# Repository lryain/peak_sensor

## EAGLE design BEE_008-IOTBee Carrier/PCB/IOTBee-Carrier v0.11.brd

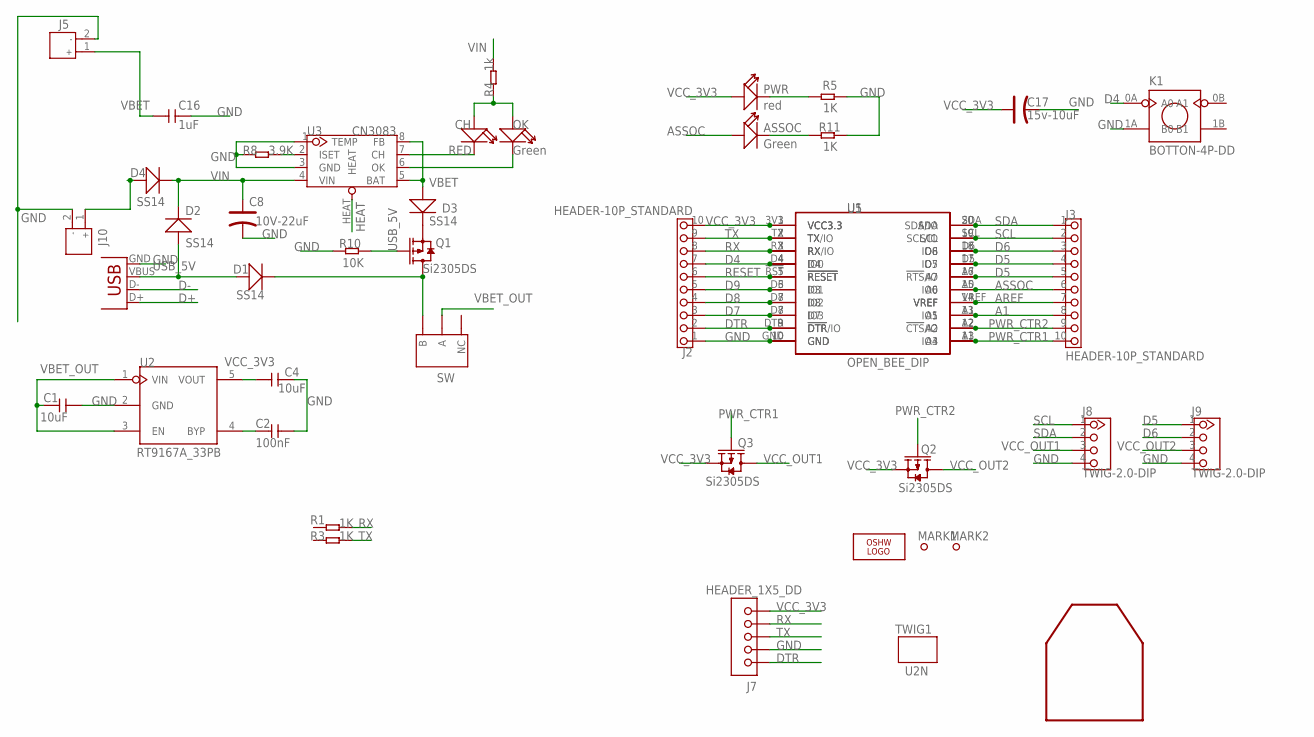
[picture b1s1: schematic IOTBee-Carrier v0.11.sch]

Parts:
ASSOC: Green; D0603
C1, C4: 10uF; 0805
C2: 100nF; 0603
C8: 10V-22uF; AVX-B
C16: 1uF; 0805
C17: 15v-10uF; AVX-A
CH: RED; D0603
D1, D2, D3, D4: SS14; D2010
J2, J3: HEADER-10P_STANDARD; 2.54_10P
J5, J10: JST-2P-POWER-LEADED; 2P-2.0-LEADED-4.7X6.0
J7: HEADER_1X5_DD; CK_1X5
J8, J9: TWIG-2.0-DIP; 2.0_1X4
K1: BOTTON-4P-DD; BTN-S
LOGO2: OSHW_LOGO_FILLX0200-NT; OSHW_FILLX200_NOTEXT
MARK1, MARK2: PAD-MARK; MARK
OK: Green; D0603
PWR: red; D0805
Q1, Q2, Q3: Si2305DS; SOT23
R1, R3, R5, R11: 1K; 0603
R4: 1k; 0603
R8: 3.9K; 0603
R10: 10K; 0603
SW: SWITCH-3P; 008-SW-3P-DIP
TWIG1: U2N; U2N_SILK
U1: OPEN_BEE_DIP; CCBEE-PRO
U2: RT9167A_33PB; SOT23-5
U3: CN3083; SOP8
U5: BEE-IOTBEE-IOTBEE-SOCKET; IOT_BEE_SMD
U$1: WIFI_SILK
X1: USB-SMD-NS; USB-MINIB-NOSTOP

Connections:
A1: J3.8, U1.13 (IO5), U5.A1
AREF: J3.7, U1.14 (VREF), U5.VREF
ASSOC: ASSOC.+, J3.6, U1.15 (IO6), U5.A0
D4: J2.7, K1.0A (A0), U1.4 (IO0), U5.D4
D5: J3.4, J3.5, J9.1, U1.16 (!RTS!/IO), U1.17 (IO7), U5.A7, U5.D5
D6: J3.3, J9.2, U1.18 (IO8), U5.D6
D7: J2.3, U1.8 (IO3), U5.D7
D8: J2.4, U1.7 (IO2), U5.D8
D9: J2.5, U1.6 (IO1), U5.D3
D+: X1.D+
D-: X1.D-
DTR: J2.2, J7.1, U1.9 (!DTR!/IO), U5.DTR (!DTR)
GND: C1.2, C2.2, C4.2, C8.-, C16.2, C17.-, J2.1, J5.2, J7.2, J8.4, J9.4, J10.2, K1.1A (B0), R5.1, R8.1, R10.1, R11.1, U1.10 (GND), U2.2 (GND), U3.1 (TEMP), U3.3 (GND), U5.GND, X1.GND
HEAT: U3.HEAT
unnamed: PWR.-, R5.2
unnamed: R8.2, U3.2 (ISET)
unnamed: D4.+, J10.1
unnamed: C2.1, U2.4 (BYP)
unnamed: CH.-, U3.7 (CH)
unnamed: OK.-, U3.6 (OK)
unnamed: CH.+, OK.+, R4.1
unnamed: D3.-, Q1.2 (S)
unnamed: ASSOC.-, R11.2
unnamed: D1.-, Q1.3 (D), SW.P$3 (B)
PWR_CTR1: J3.10, Q3.1 (G), U1.11 (IO4), U5.A3
PWR_CTR2: J3.9, Q2.1 (G), U1.12 (!CTS!/IO), U5.A2
RESET: J2.6, U1.5 (!RESET), U5.!RST (!RESET)
RX: J2.8, J7.4, R1.2, U1.3 (RX/IO), U5.RX
SCL: J3.2, J8.1, U1.19 (SCL/IO), U5.SCL
SDA: J3.1, J8.2, U1.20 (SDA/IO), U5.SDA
TX: J2.9, J7.3, R3.2, U1.2 (TX/IO), U5.TX
USB_5V: D1.+, D2.+, Q1.1 (G), R10.2, X1.VBUS
VBET: C16.1, D3.+, J5.1, U3.5 (BAT), U3.8 (FB)
VBET_OUT: C1.1, SW.P$2 (A), U2.1 (VIN), U2.3 (EN)
VCC_3V3: C4.1, C17.+, J2.10, J7.5, PWR.+, Q2.2 (S), Q3.2 (S), U1.1 (VCC3.3), U2.5 (VOUT), U5.3V3 (VCC3.3)
VCC_OUT1: J8.3, Q3.3 (D)
VCC_OUT2: J9.3, Q2.3 (D)
VIN: C8.+, D2.-, D4.-, R4.2, U3.4 (VIN)

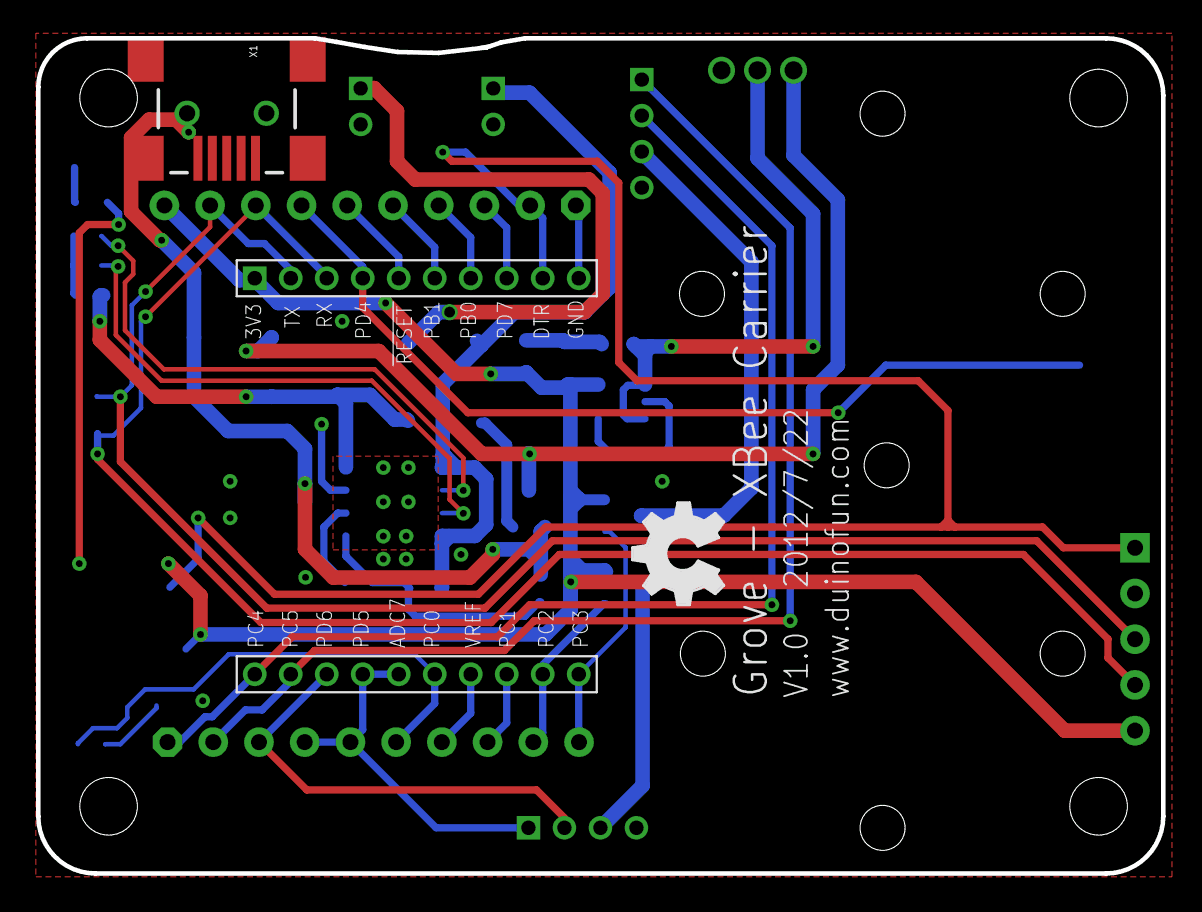
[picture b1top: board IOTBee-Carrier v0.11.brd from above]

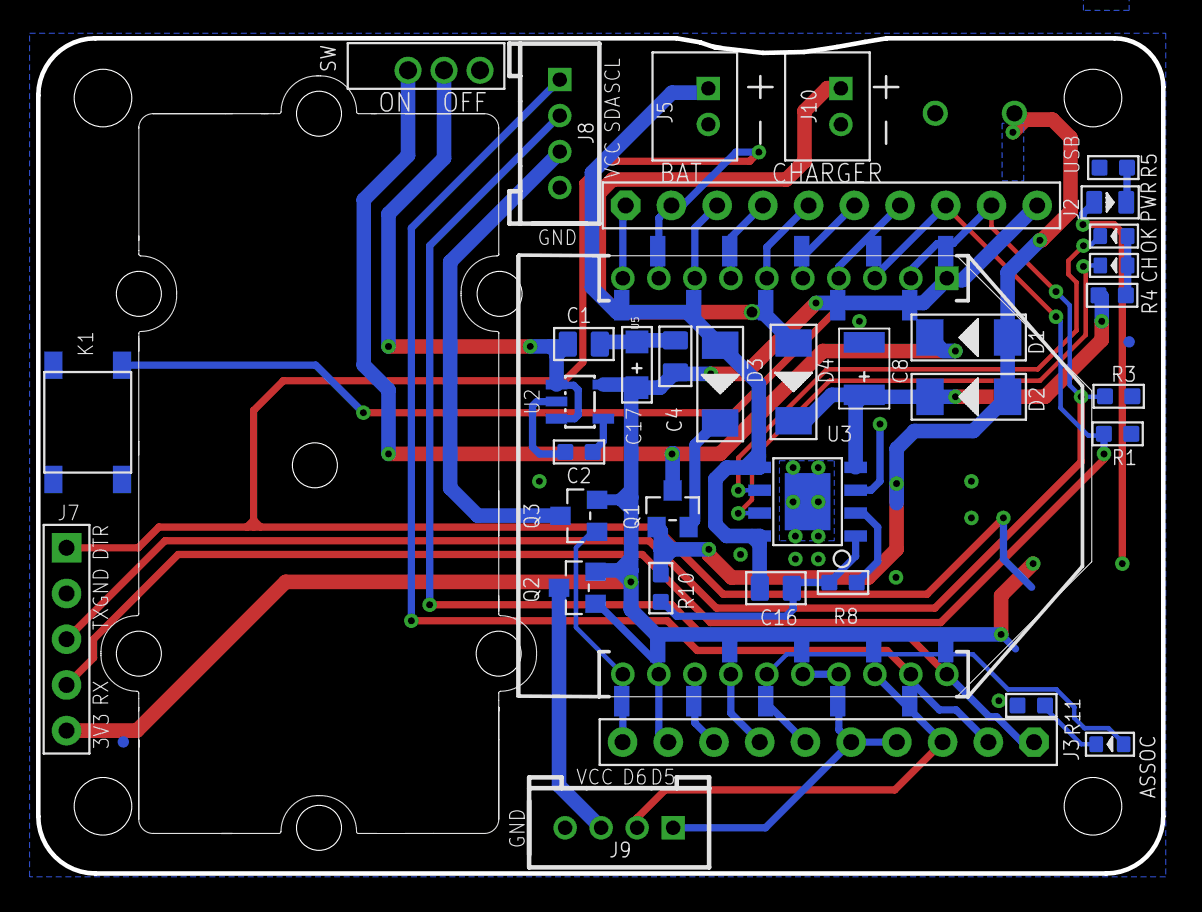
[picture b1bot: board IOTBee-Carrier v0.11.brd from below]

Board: 2 copper layers, 62.5 x 46.5 mm, 43 parts (41 on the bottom side), 35 nets.

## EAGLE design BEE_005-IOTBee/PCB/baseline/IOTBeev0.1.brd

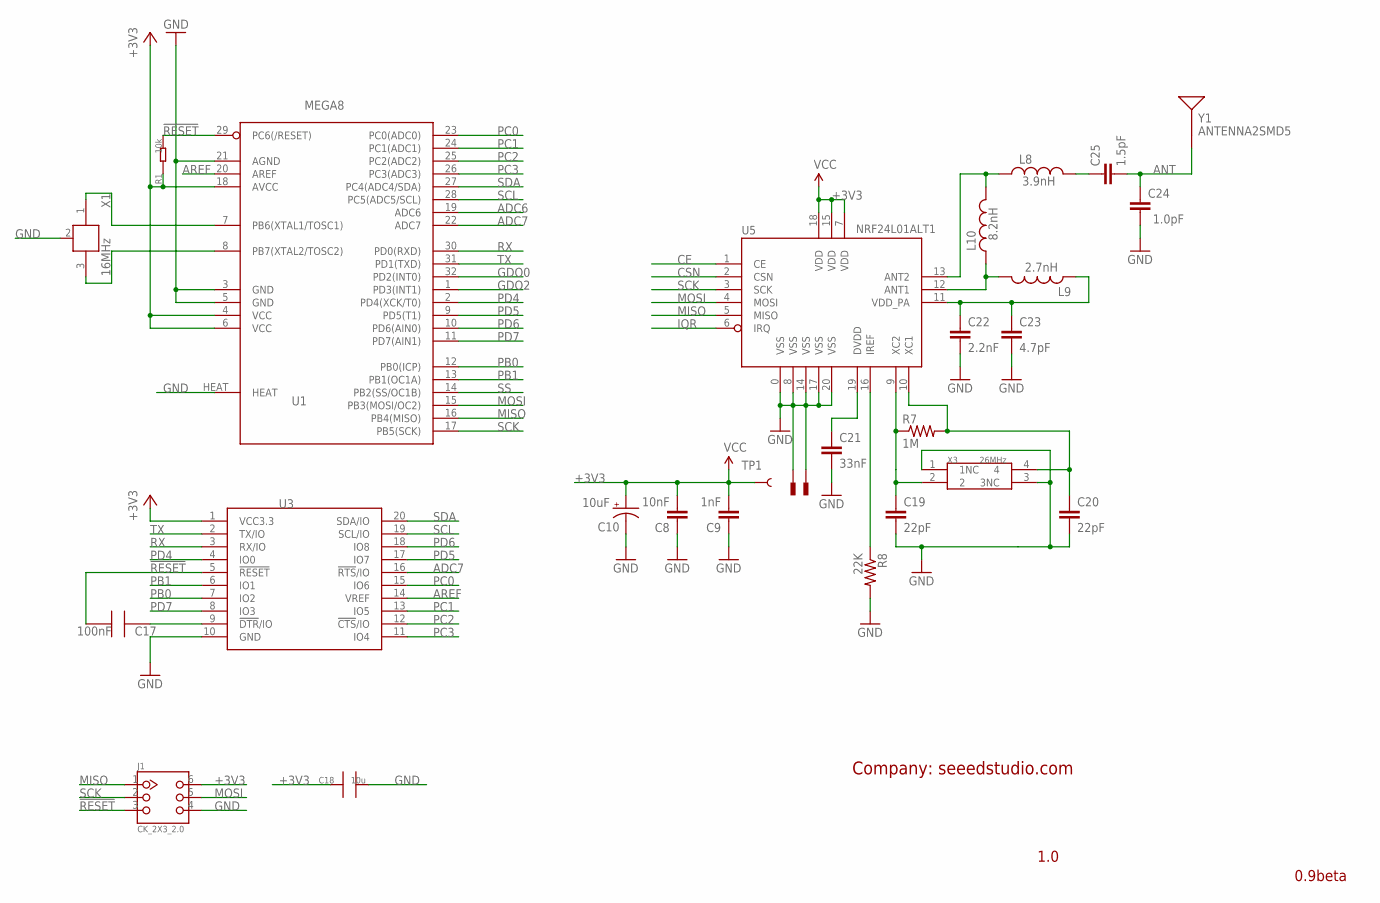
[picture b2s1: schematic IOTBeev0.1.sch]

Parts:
C8: 10nF; 0402-CAP
C9: 1nF; 0402-CAP
C10: 10uF; EIA3528
C17: 100nF; 0603_S
C18: 10u; 0805
C19, C20: 22pF; 0402-CAP
C21: 33nF; 0402-CAP
C22: 2.2nF; 0402-CAP
C23: 4.7pF; 0402-CAP
C24: 1.0pF; 0402-CAP
C25: 1.5pF; 0402-CAP
J1: CK_2X3_2.0
L8: 3.9nH; C0402
L9: 2.7nH; C0402
L10: 8.2nH; C0402
R1: 10k; 0603_S
R7: 1M; 0402-RES
R8: 22K; 0402-RES
TP1: TEST-POINT3X5; PAD.03X.05
U1: MEGA8; MLF32X
U3: BEE-OPENBEE-BTSMD; 20P-SMD-2.0-BT
U5: NRF24L01ALT1; QFN20_ALT1
U$2, U$4: PAD; PAD-0.008
X1: 16MHz; XTAL_3X2
X3: 26MHz; X3225
Y1: ANTENNA2SMD5; ANTENNA-CHIP5

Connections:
!RESET: C17.2, J1.3, R1.2, U1.29 (PC6(/RESET)), U3.5 (!RESET)
+3V3: C8.2, C9.2, C10.A (+), C18.1, J1.6, R1.1, TP1.P$1, U1.4 (VCC), U1.6 (VCC), U1.18 (AVCC), U3.1 (VCC3.3), U5.7 (VDD), U5.15 (VDD), U5.18 (VDD)
ADC6: U1.19 (ADC6)
ADC7: U1.22 (ADC7), U3.16 (!RTS!/IO)
ANT: C24.2, C25.2, Y1.FEED
AREF: U1.20 (AREF), U3.14 (VREF)
CE: U5.1 (CE)
CSN: U5.2 (CSN)
DTR: C17.1, U3.9 (!DTR!/IO)
GDO0: U1.32 (PD2(INT0))
GDO2: U1.1 (PD3(INT1))
GND: C8.1, C9.1, C10.C (-), C18.2, C19.2, C20.2, C21.2, C22.2, C23.2, C24.1, J1.4, R8.2, U1.3 (GND), U1.5 (GND), U1.21 (AGND), U1.HEAT, U3.10 (GND), U5.0 (VSS), U5.8 (VSS), U5.14 (VSS), U5.17 (VSS), U5.20 (VSS), U$2.P$1, U$4.P$1, X1.2 (GND), X3.1 (1NC), X3.3 (3NC)
IQR: U5.6 (IRQ)
MISO: J1.1, U1.16 (PB4(MISO)), U5.5 (MISO)
MOSI: J1.5, U1.15 (PB3(MOSI/OC2)), U5.4 (MOSI)
unnamed: U1.7 (PB6(XTAL1/TOSC1)), X1.1
unnamed: U1.8 (PB7(XTAL2/TOSC2)), X1.3 (2)
unnamed: C19.1, R7.1, U5.9 (XC2), X3.2
unnamed: C20.1, R7.2, U5.10 (XC1), X3.4
unnamed: L8.1, L10.2, U5.13 (ANT2)
unnamed: C22.1, C23.1, L9.1, U5.11 (VDD_PA)
unnamed: R8.1, U5.16 (IREF)
unnamed: C21.1, U5.19 (DVDD)
unnamed: L9.2, L10.1, U5.12 (ANT1)
unnamed: C25.1, L8.2
PB0: U1.12 (PB0(ICP)), U3.7 (IO2)
PB1: U1.13 (PB1(OC1A)), U3.6 (IO1)
PC0: U1.23 (PC0(ADC0)), U3.15 (IO6)
PC1: U1.24 (PC1(ADC1)), U3.13 (IO5)
PC2: U1.25 (PC2(ADC2)), U3.12 (!CTS!/IO)
PC3: U1.26 (PC3(ADC3)), U3.11 (IO4)
PD4: U1.2 (PD4(XCK/T0)), U3.4 (IO0)
PD5: U1.9 (PD5(T1)), U3.17 (IO7)
PD6: U1.10 (PD6(AIN0)), U3.18 (IO8)
PD7: U1.11 (PD7(AIN1)), U3.8 (IO3)
RX: U1.30 (PD0(RXD)), U3.3 (RX/IO)
SCK: J1.2, U1.17 (PB5(SCK)), U5.3 (SCK)
SCL: U1.28 (PC5(ADC5/SCL)), U3.19 (SCL/IO)
SDA: U1.27 (PC4(ADC4/SDA)), U3.20 (SDA/IO)
SS: U1.14 (PB2(SS/OC1B))
TX: U1.31 (PD1(TXD)), U3.2 (TX/IO)

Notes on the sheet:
0.9beta
1.0
Company: seeedstudio.com

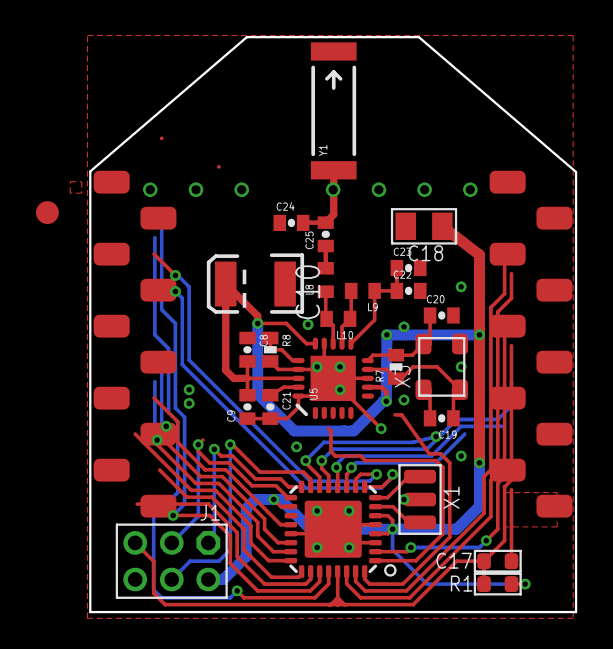
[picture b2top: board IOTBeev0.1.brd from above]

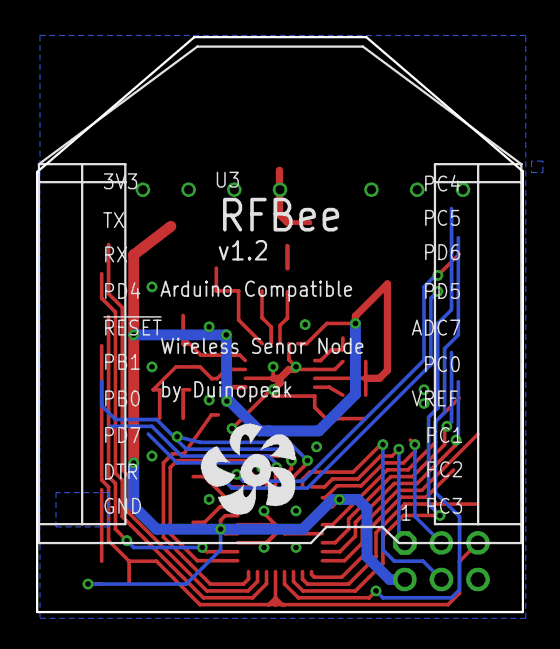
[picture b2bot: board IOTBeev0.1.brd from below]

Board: 2 copper layers, 27.0 x 31.9 mm, 29 parts (2 on the bottom side), 34 nets.

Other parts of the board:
U$1: DUINOFUN-LOGO-PCB-0.7

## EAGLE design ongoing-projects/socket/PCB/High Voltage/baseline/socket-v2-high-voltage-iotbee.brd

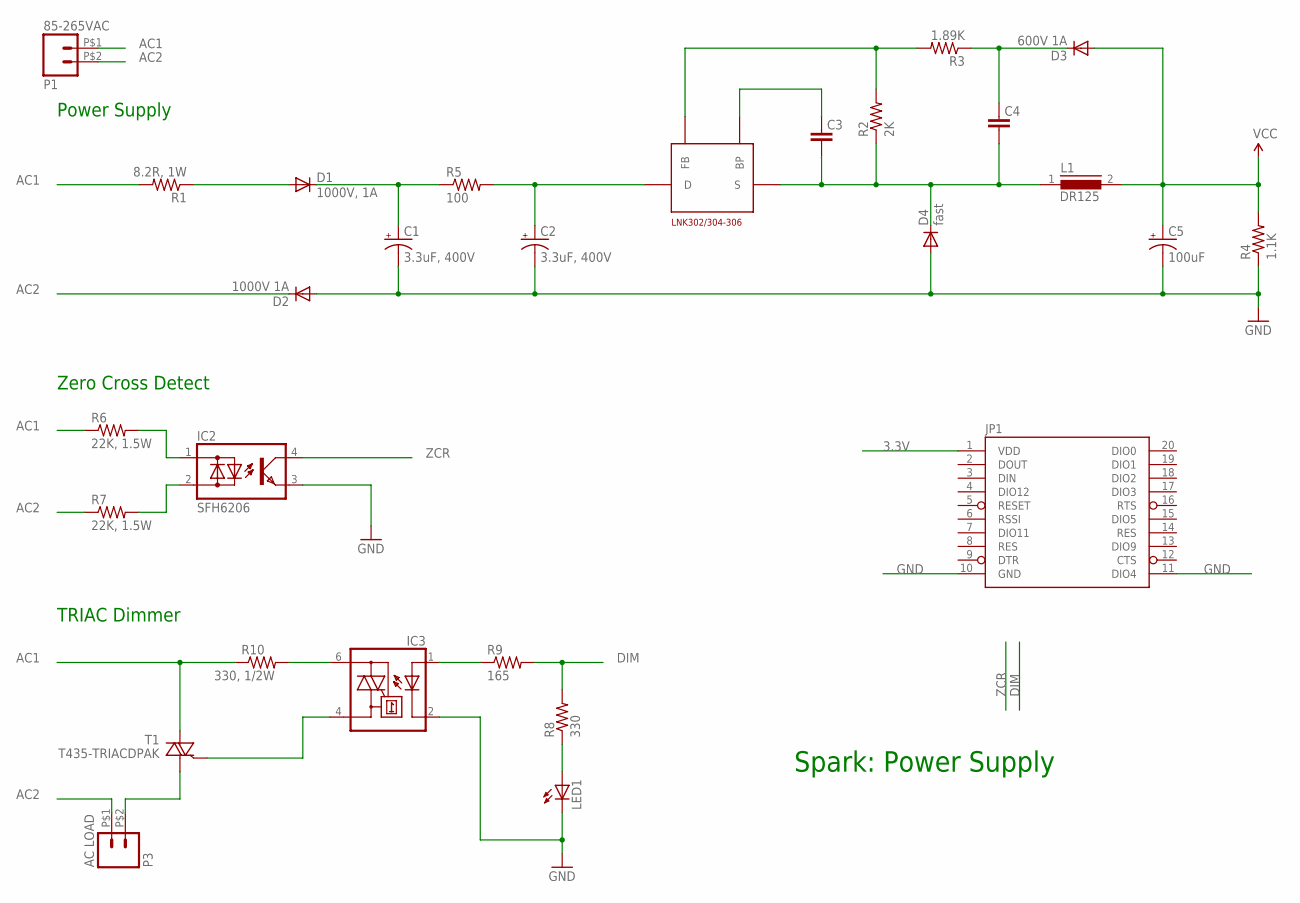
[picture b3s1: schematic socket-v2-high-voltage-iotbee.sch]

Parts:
C1, C2: 3.3uF, 400V; E3,5-8
C3: 0.1uF; 0603-CAP
C4: 10uF, 50V; 0805
C5: 100uF; EIA3528
D1: 1000V, 1A; SMA-DIODE
D2: 1000V 1A; SMA-DIODE
D3: 600V 1A; SMA-DIODE
D4: fast; SMA-DIODE
IC1: LNK302/304-306; SMD-8B
IC2: SFH6206; DIL4-SMD
IC3: MOC3031S; DIL6-SMD; MPN MOC3031SM
JP1: XBEE-1B3; XBEE-SMD
L1: DR125
LED1: LED0603; LED-0603
P1: 85-265VAC; 1X02_BIG
P3: AC LOAD; 1X02_BIG
R1: 8.2R, 1W; 0207/10
R2: 2K; 0805
R3: 1.89K; 0805
R4: 1.1K; 0603-RES
R5: 100; 0204/7
R6, R7: 22K, 1.5W; R2512
R8: 330; 0805
R9: 165; 0805
R10: 330, 1/2W; R1210
T1: T435-TRIACDPAK; TO252

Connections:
3.3V: C5.A (+), D3.A, JP1.1 (VDD), L1.2, R4.2
$N$100: C3.1, C4.1, D4.C, IC1.S1 (S), L1.1, R2.1
$N$101: C2.+, IC1.D, R5.2
AC1: P1.P$1 (1), R1.2, R6.1, R10.1, T1.2 (A2)
AC2: D2.C, P1.P$2 (2), P3.P$1 (1), R7.1
DIM: R8.2, R9.2
GND: C1.-, C2.-, C5.C (-), D2.A, D4.A, IC2.3 (E), IC3.2 (C), JP1.10 (GND), JP1.11 (DIO4), LED1.C, R4.1
unnamed: C4.2, D3.C, R3.1
unnamed: C3.2, IC1.BP
unnamed: IC3.1 (A), R9.1
unnamed: IC3.6 (A2), R10.2
unnamed: IC3.4 (A1), T1.3 (G)
unnamed: P3.P$2 (2), T1.1 (A1)
unnamed: IC2.1 (AC1), R6.2
unnamed: LED1.A, R8.1
unnamed: C1.+, D1.C, R5.1
unnamed: IC1.FB, R2.2, R3.2
unnamed: IC2.2 (AC2), R7.2
RAW_PR: D1.A, R1.1
ZCR: IC2.4 (C)

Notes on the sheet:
Power Supply
Spark: Power Supply
Zero Cross Detect
TRIAC Dimmer

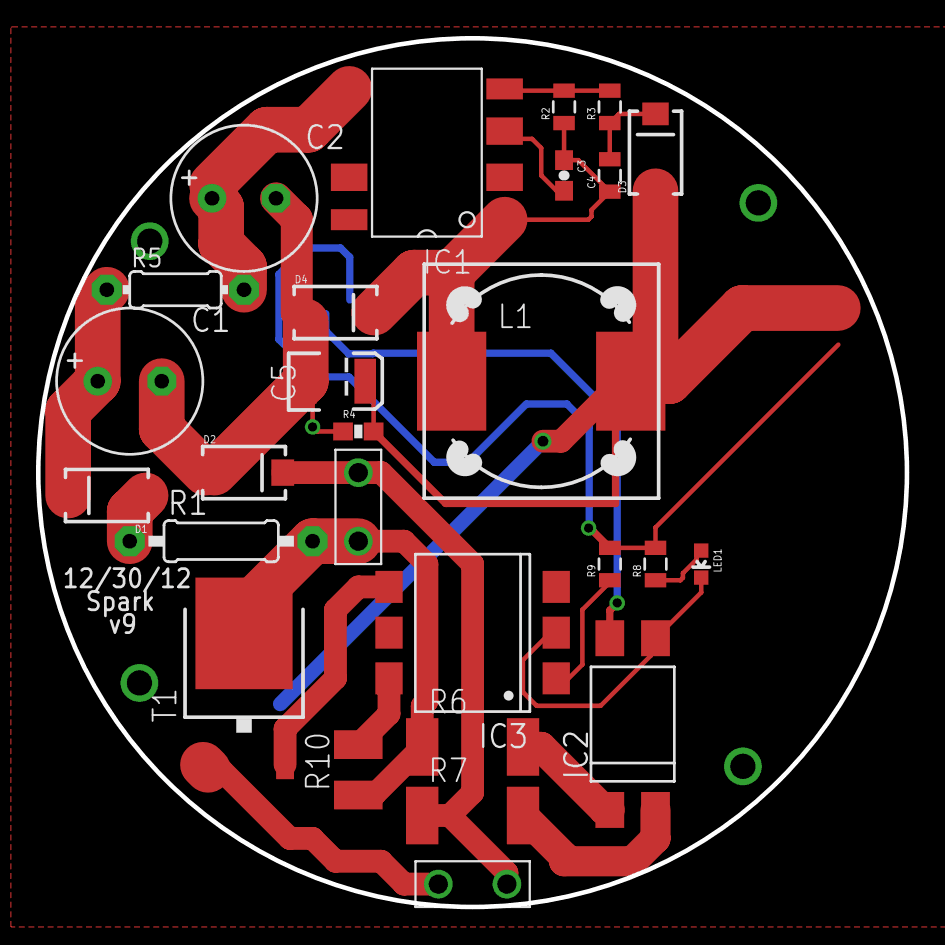
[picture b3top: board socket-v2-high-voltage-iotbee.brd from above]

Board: 2 copper layers, 48.3 x 48.3 mm, 28 parts (1 on the bottom side), 19 nets.

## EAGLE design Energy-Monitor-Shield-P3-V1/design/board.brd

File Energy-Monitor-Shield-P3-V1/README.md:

Energy Monitor Shield P3 is an Arduino-compatible expansion card designed for building energy monitoring system with LCD screen and an interface for connecting the wireless transceiver nRF24L01 +.
 
Connect up to three sensors AC (30-100A)

Support for LCD Screen Nokia LCD5110

Turn off the LCD backlight with a jumper

Two buttons to control (operate one analog pin)

Interface to connect the transceiver to 2.4G nRF24L01 +

GROVE-compatible connector: I2C

Fully compatible with Ethernet Shield

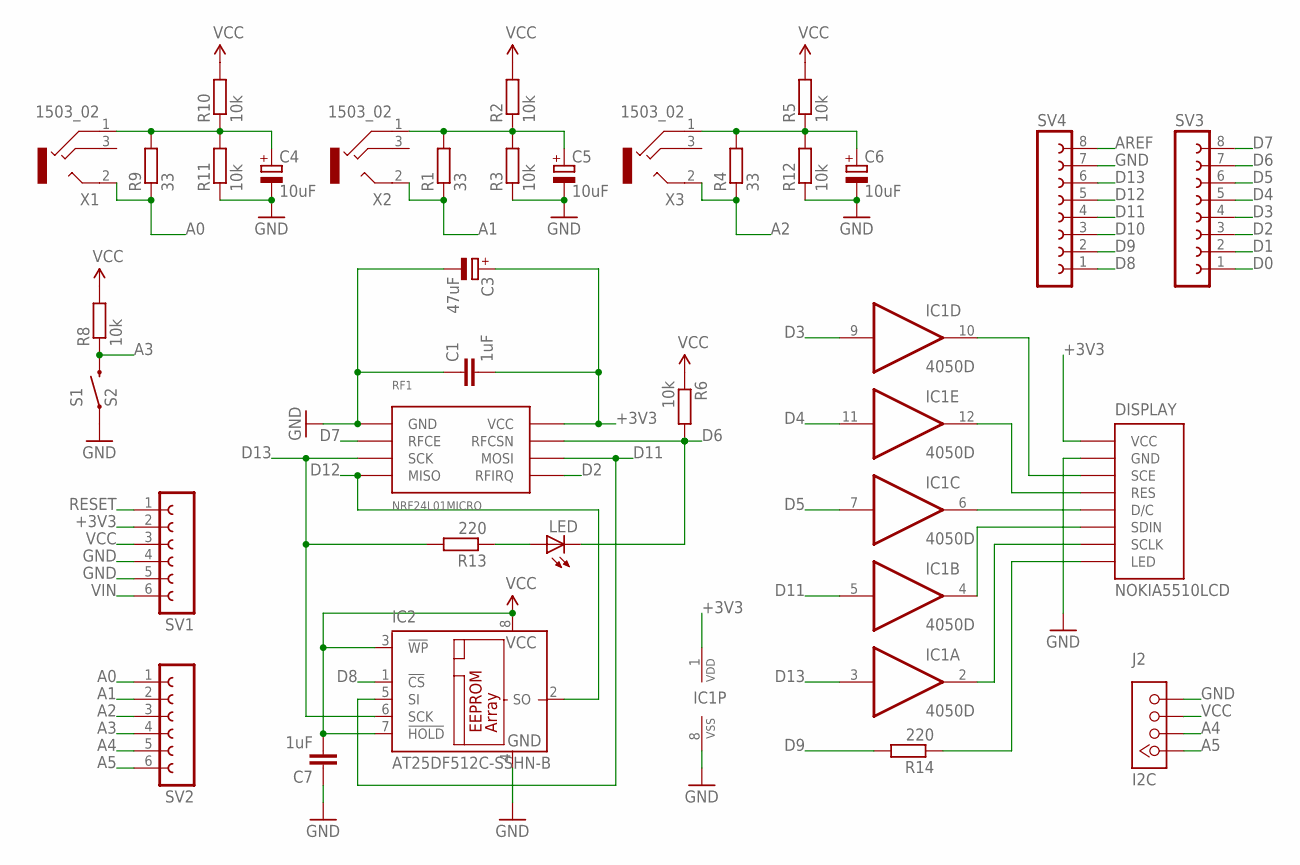
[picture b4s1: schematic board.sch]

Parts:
C1, C7: 1uF; C0805
C3: 47uF; 153CLV-0405
C4, C5, C6: 10uF; 153CLV-0405
DISPLAY: NOKIA5510LCD; NOKIA5510LCD-BLUE
IC1: 4050D; SO16
IC2: AT25DF512C-SSHN-B; SO-08
J2: I2C; TWIG-4P-2.0C
LED: LEDCHIPLED_0805; CHIPLED_0805
R1, R4, R9: 33; M0805
R2, R3, R5, R6, R8, R10, R11, R12: 10k; M0805
R13, R14: 220; M0805
RF1: NRF24L01MICRO; MICRO-RF24
S1: S2; TACTILE-PTH-SIDEEZ
SV1, SV2: FE06-1; FE06
SV3, SV4: FE08-1; FE08
X1, X2, X3: 1503_02

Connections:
1: C4.+, R9.2, R10.1, R11.2, X1.1
2: C5.+, R1.2, R2.1, R3.2, X2.1
3: C6.+, R4.2, R5.1, R12.2, X3.1
+3V3: C1.2, C3.+, DISPLAY.VCC, IC1.1 (VDD), RF1.3V3 (VCC), SV1.2
A0: R9.1, SV2.1, X1.2
A1: R1.1, SV2.2, X2.2
A2: R4.1, SV2.3, X3.2
A3: R8.1, S1.2, SV2.4
A4: J2.P$2, SV2.5
A5: J2.P$1, SV2.6
AREF: SV4.8
CSE: DISPLAY.CE (SCE), IC1.10 (O)
D0: SV3.1
D1: SV3.2
D2: RF1.IRQ (RFIRQ), SV3.3
D3: IC1.9 (I), SV3.4
D4: IC1.11 (I), SV3.5
D5: IC1.7 (I), SV3.6
D6: LED.C, R6.2, RF1.CSN (RFCSN), SV3.7
D7: RF1.CE (RFCE), SV3.8
D8: IC2.1 (!CS), SV4.1
D9: R14.2, SV4.2
D10: SV4.3
D11: IC1.5 (I), IC2.5 (SI), RF1.MOSI, SV4.4
D12: IC2.2 (SO), RF1.MISO, SV4.5
D13: IC1.3 (I), IC2.6 (SCK), R13.2, RF1.SCK, SV4.6
GND: C1.1, C3.-, C4.-, C5.-, C6.-, C7.1, DISPLAY.GND, IC1.8 (VSS), IC2.4 (GND), J2.P$4, R3.1, R11.1, R12.1, RF1.GND, S1.1, SV1.4, SV1.5, SV4.7
unnamed: DISPLAY.BL (LED), R14.1
unnamed: LED.A, R13.1
unnamed: DISPLAY.DC (D/C), IC1.6 (O)
unnamed: DISPLAY.DIN (SDIN), IC1.4 (O)
unnamed: DISPLAY.CLK (SCLK), IC1.2 (O)
RESET: SV1.1
RST: DISPLAY.RST (RES), IC1.12 (O)
VCC: C7.2, IC2.3 (!WP), IC2.7 (!HOLD), IC2.8 (VCC), J2.P$3, R2.2, R5.2, R6.1, R8.2, R10.2, SV1.3
VIN: SV1.6

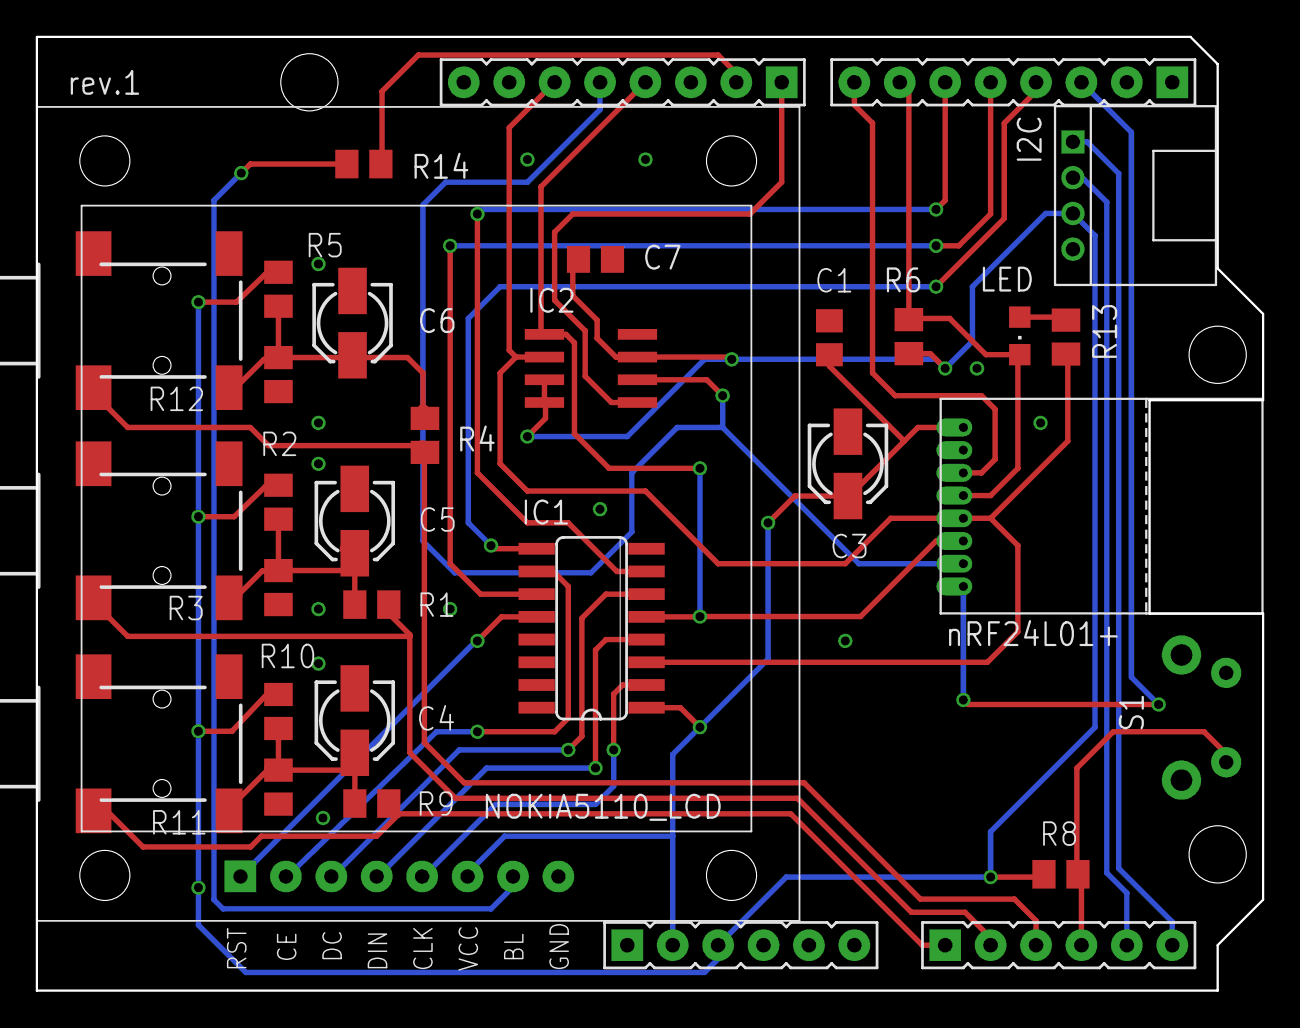
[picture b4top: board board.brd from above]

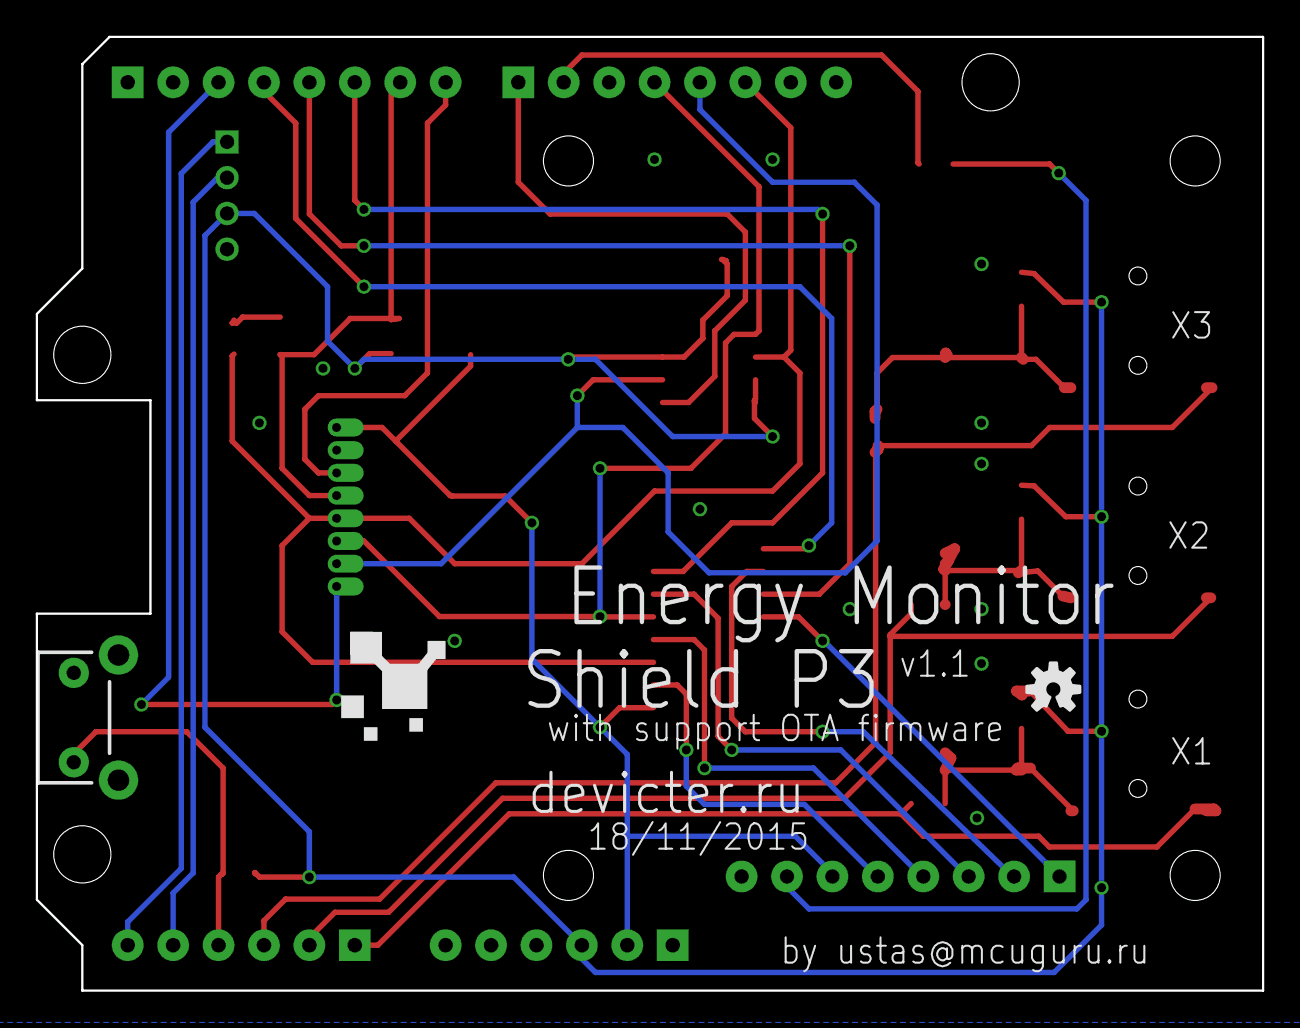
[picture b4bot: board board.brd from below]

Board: 2 copper layers, 68.6 x 53.3 mm, 34 parts (2 on the bottom side), 30 nets.

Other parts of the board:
U$2: OSHW-LOGO-S

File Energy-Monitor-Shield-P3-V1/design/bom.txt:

Assembly variant: 

Part    Value             Device                    Package            Description                                   
C1      1uF               C-EUC0805                 C0805              CAPACITOR, European symbol                    
C3      47uF              CPOL-EU153CLV-0405        153CLV-0405        POLARIZED CAPACITOR, European symbol          
C4      10uF              CPOL-EU153CLV-0405        153CLV-0405        POLARIZED CAPACITOR, European symbol          
C5      10uF              CPOL-EU153CLV-0405        153CLV-0405        POLARIZED CAPACITOR, European symbol          
C6      10uF              CPOL-EU153CLV-0405        153CLV-0405        POLARIZED CAPACITOR, European symbol          
C7      1uF               C-EUC0805                 C0805              CAPACITOR, European symbol                    
DISPLAY NOKIA5510LCD      NOKIA5510LCD-BLUE         NOKIA5510LCD-BLUE                                                
IC1     4050D             4050D                     SO16               Hex non-inverting BUFFER                      
IC2     AT25DF512C-SSHN-B 25AA080SN                 SO-08              Serial EEPROM 4K/ 8K , SPI bus                
J2      I2C               TWIG-4P-2.0C              TWIG-4P-2.0C                                                     
LED                       LEDCHIPLED_0805           CHIPLED_0805       LED                                           
R1      33                R-EU_M0805                M0805              RESISTOR, European symbol                     
R2      10k               R-EU_M0805                M0805              RESISTOR, European symbol                     
R3      10k               R-EU_M0805                M0805              RESISTOR, European symbol                     
R4      33                R-EU_M0805                M0805              RESISTOR, European symbol                     
R5      10k               R-EU_M0805                M0805              RESISTOR, European symbol                     
R6      10k               R-EU_M0805                M0805              RESISTOR, European symbol                     
R8      10k               R-EU_M0805                M0805              RESISTOR, European symbol                     
R9      33                R-EU_M0805                M0805              RESISTOR, European symbol                     
R10     10k               R-EU_M0805                M0805              RESISTOR, European symbol                     
R11     10k               R-EU_M0805                M0805              RESISTOR, European symbol                     
R12     10k               R-EU_M0805                M0805              RESISTOR, European symbol                     
R13     220               R-EU_M0805                M0805              RESISTOR, European symbol                     
R14     220               R-EU_M0805                M0805              RESISTOR, European symbol                     
RF1     NRF24L01MICRO     NRF24L01MICRO             MICRO-RF24                                                       
S1      S2                SWITCH-MOMENTARY-2SIDE_EZ TACTILE-PTH-SIDEEZ Various NO switches- pushbuttons, reed, etc   
SV1                       FE06-1                    FE06               FEMALE HEADER                                 
SV2                       FE06-1                    FE06               FEMALE HEADER                                 
SV3                       FE08-1                    FE08               FEMALE HEADER                                 
SV4                       FE08-1                    FE08               FEMALE HEADER                                 
X1      1503_02           1503_02                   1503_02            Jack connectors according to JISC 6560, 3.5 mm
X2      1503_02           1503_02                   1503_02            Jack connectors according to JISC 6560, 3.5 mm
X3      1503_02           1503_02                   1503_02            Jack connectors according to JISC 6560, 3.5 mm

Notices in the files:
In-Wall-ACDC-Pcb-with-Relay-for-MySensors-SMD/design/InWallPCB7smd.brd:
Licensed under CERN OHL v.1.2
parts and their libraries:
SparkFun-Connectors: Licensing: CC v3.0 Share-Alike You are welcome to use this library for commercial purposes.
SparkFun-Capacitors: Licensing: Creative Commons ShareAlike 4.0 International - https://creativecommons.org/licenses/by-sa/4.0
